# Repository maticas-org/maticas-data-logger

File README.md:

# Maticas datalogger 🚀⭐️

Want to send measurements back to a server through HTTP or MQTT? This is about it along with:

- The PCB design 🤖.
    - The schematic.
    - The PCB layout.
    - Source files for KiCad.
- 3D design 🗿:
    - The enclosure.
    - The sensor holder, stevenson screen.
- Code for the ESP32 💻.
    - Arduino code.

### ESP32 [Bee-Data-Logger](https://github.com/strid3r21/Bee-Data-Logger) Based 🐝

The ESP32 Bee-Data-Logger based solution is a data logger based on the development from [them](https://github.com/strid3r21/Bee-Data-Logger).

It is intended to be final product, we grabbed the schematic pdf they provided and made a PCB design for it, sharing the KiCad files and the Gerber files, so you can make your own PCB, or have an easier time modifying the design.

If you want to find out more about the ESP32 Bee-Data-Logger based solution, check out the [ESP32 Bee-Data-Logger based PCB design doc](/pcb/datalogger-bee-based/).

### ESP32 Dev Board 🔧

The ESP32 Dev Board is a development board with an ESP32 microcontroller. Intended for prototyping and development, but you could use it for a final product. 

If want to find out more about the ESP32 Dev Board, check out the [ESP32 Dev Board code](/src/arduino/datalogger-esp32-dev-board/) and the [ESP32 Dev Board PCB design doc](/pcb/datalogger-esp32-dev-board/).

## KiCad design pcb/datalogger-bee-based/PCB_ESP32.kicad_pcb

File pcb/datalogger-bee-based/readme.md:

# This file is inspired on the work of the [Bee-Data-Logger](https://github.com/strid3r21/Bee-Data-Logger) project

Basically we took the schematics they shared and a bit of the layout we get from their [youtube video](https://youtu.be/vbtSqaVAqRw?si=KjJlswMw_XBVi3_l) and we made our own version of the datalogger, sharing the source files from kiCad to make it easier for others to replicate the project.

This PCB replica is undergoing testing and will be updated as soon as we have more information.

Huge thanks to the [Bee-Data-Logger](https://github.com/strid3r21/Bee-Data-Logger) project for sharing their work, it was a great inspiration for us, and a huge help to get started with our own datalogger project. Go check their project out! Give them a star️ ⭐️⭐️⭐! 

Please consider that the latest finished PCB version is [PCB_ESP32.kicad_pro](PCB_ESP32.kicad_pro), this is built on top of Kicad 8.0. So far we don't have code along for this project, so if you are interested in replicating this project, you will need to adapt the code from the [Bee-Data-Logger](https://github.com/strid3r21/Bee-Data-Logger)

## Schematics

## PCB Overview

## PCB 3D View

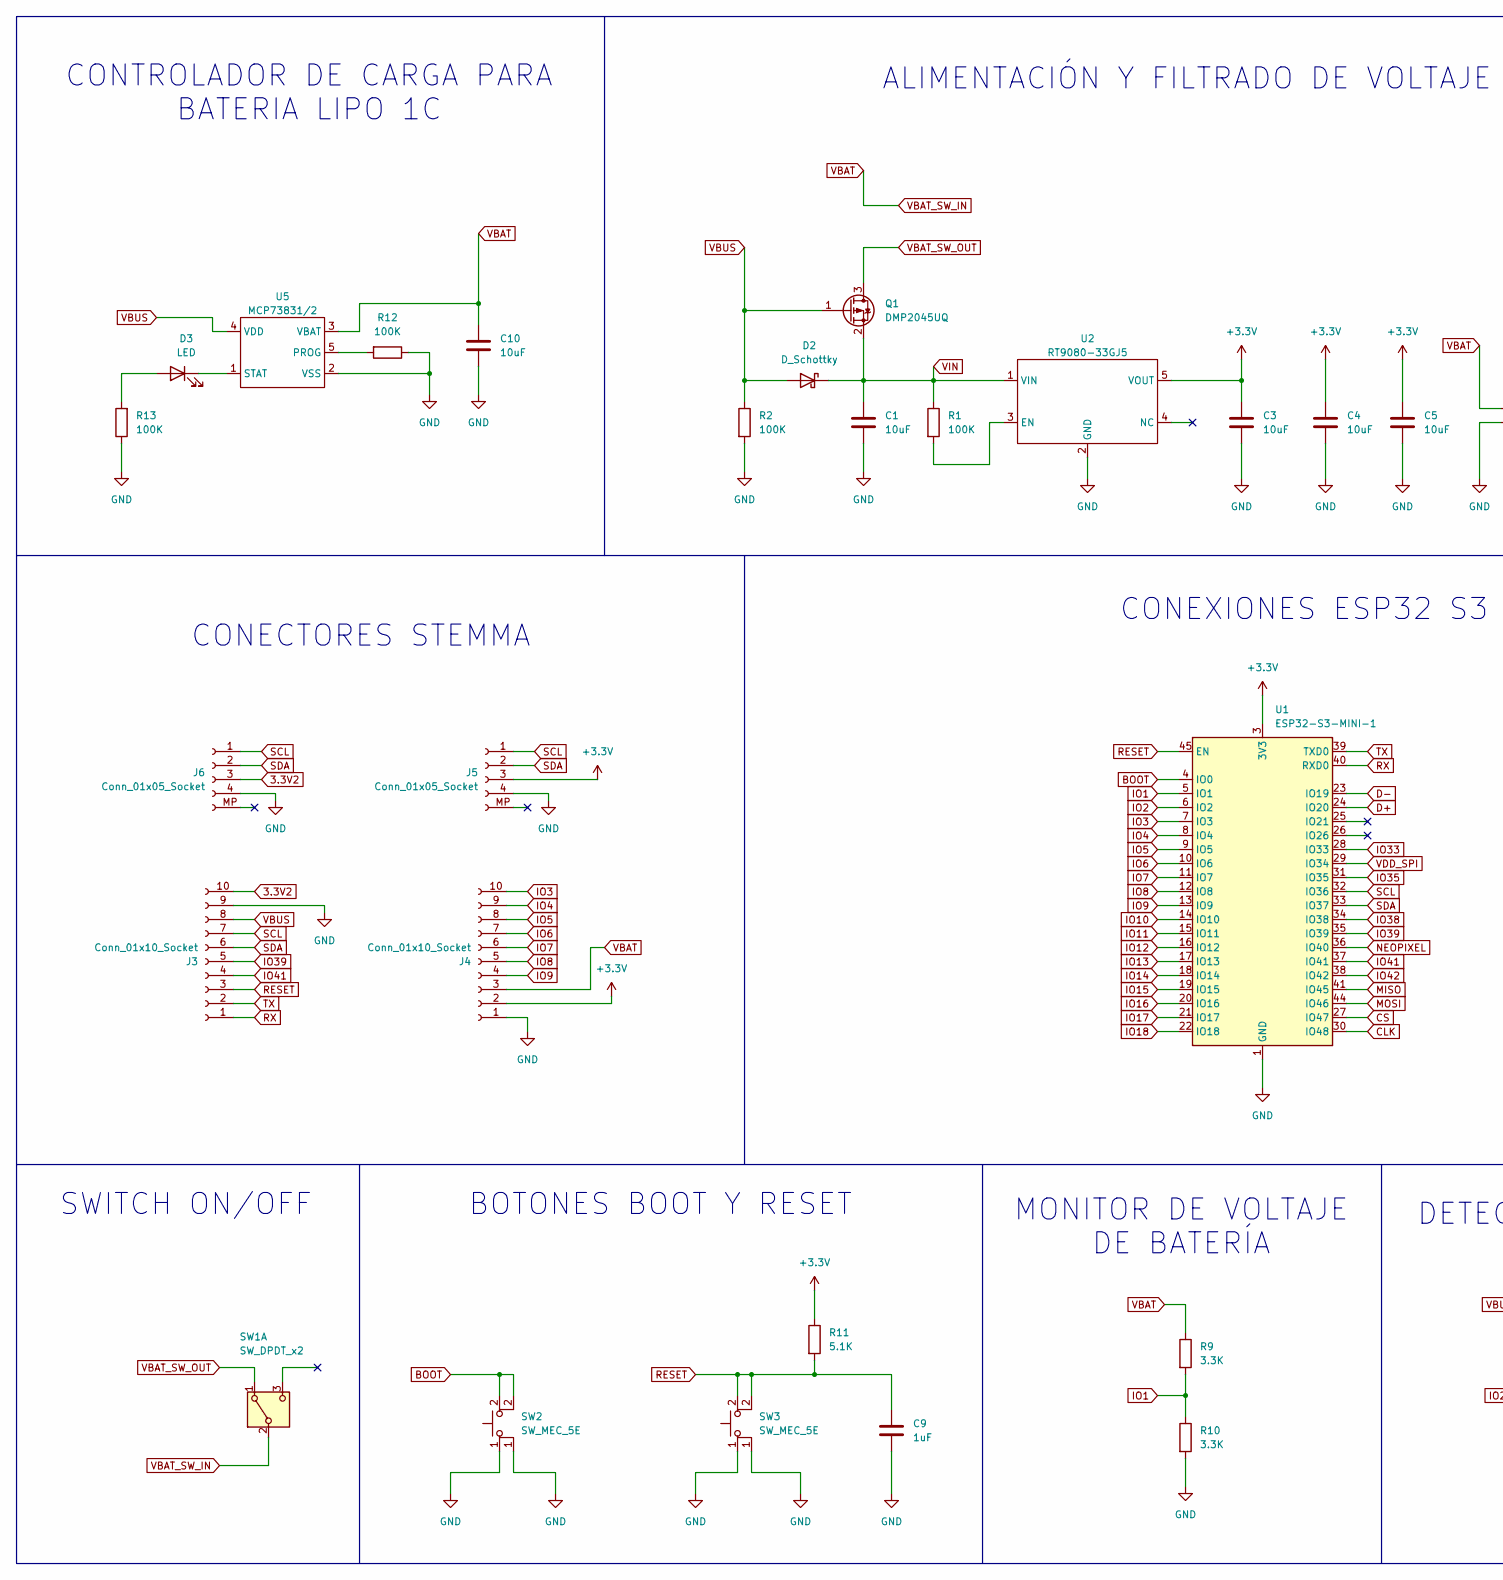
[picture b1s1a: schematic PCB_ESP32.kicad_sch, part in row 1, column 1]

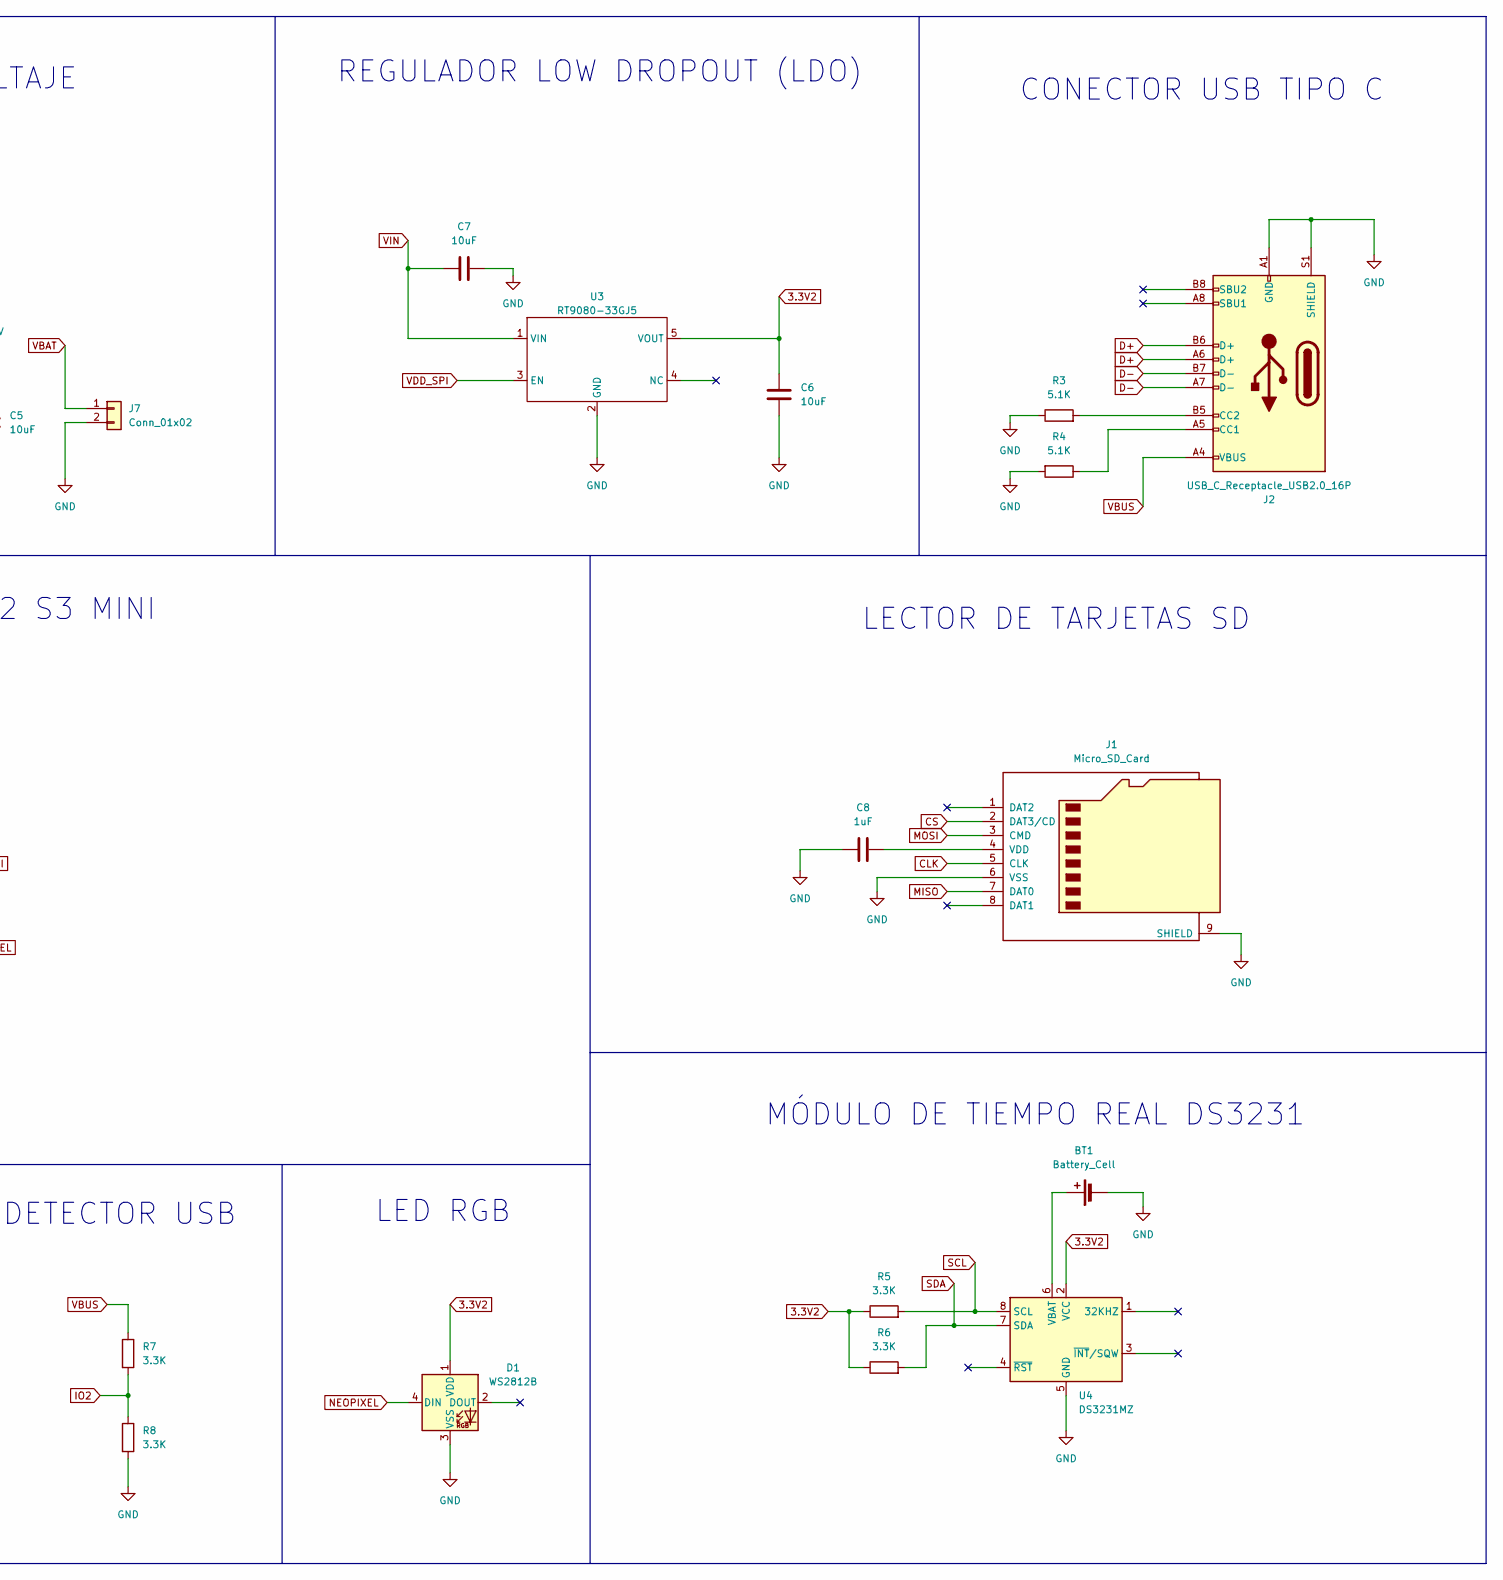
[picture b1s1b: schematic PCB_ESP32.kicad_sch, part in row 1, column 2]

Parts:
BT1: Battery_Cell; BatteryHolder_Keystone_1060_1x2032
C1, C3, C4, C5, C6, C7, C10: 10uF; C_0603_1608Metric
C8, C9: 1uF; C_0603_1608Metric
D1: WS2812B; LED_WS2812B-2020_PLCC4_2.0x2.0mm
D2: D_Schottky; DO-214AC
D3: LED; LED_0603_1608Metric
J1: Micro_SD_Card; microSD_HC_Hirose_DM3BT-DSF-PEJS
J2: USB_C_Receptacle_USB2.0_16P; USB_C_Receptacle_XKB_U262-16XN-4BVC11
J3, J4: Conn_01x10_Socket; PinHeader_1x10_P2.54mm_Vertical
J5, J6: Conn_01x05_Socket; JST_ACH_BM04B-ACHSS-A-GAN-ETF_1x04-1MP_P1.20mm_Vertical
J7: Conn_01x02; JST_ACH_BM02B-ACHSS-GAN-ETF_1x02-1MP_P1.20mm_Vertical
Q1: DMP2045UQ; SOT-23
R1, R2, R12, R13: 100K; R_0603_1608Metric
R3, R4, R11: 5.1K; R_0603_1608Metric
R5, R6, R7, R8, R9, R10: 3.3K; R_0603_1608Metric
SW1: SW_DPDT_x2; SW_SPDT_CK_JS102011SAQN
SW2, SW3: SW_MEC_5E; SW_SPST_PTS810
U1: ESP32-S3-MINI-1; ESP32-S2-MINI-1
U2, U3: RT9080-33GJ5; TSOT-23-5
U4: DS3231MZ; SOIC-8_3.9x4.9mm_P1.27mm
U5: MCP73831/2; SOT-23-5

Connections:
3.3V2: C6.1, D1.1 (VDD), J3.10, J6.3, R5.1, R6.1, U3.5 (VOUT), U4.2 (VCC)
+3.3V: C3.1, C4.1, C5.1, J4.2, J5.3, R11.1, U1.3 (3V3), U2.5 (VOUT)
BOOT: SW2.2, U1.4 (IO0)
CLK: J1.5 (CLK), U1.30 (IO48)
CS: J1.2 (DAT3/CD), U1.27 (IO47)
D+: J2.A6 (D+), J2.B6 (D+), U1.24 (IO20)
D-: J2.A7 (D-), J2.B7 (D-), U1.23 (IO19)
GND: BT1.2 (-), C1.2, C3.2, C4.2, C5.2, C6.2, C7.2, C8.1, C9.2, C10.2, D1.3 (VSS), J1.6 (VSS), J1.9 (SHIELD), J2.A1 (GND), J2.A12 (GND), J2.B1 (GND), J2.B12 (GND), J2.S1 (SHIELD), J3.9, J4.1, J5.4, J6.4, J7.2, R2.2, R3.1, R4.2, R8.2, R10.2, R12.1, R13.1, SW2.1, SW3.1, U1.1 (GND), U1.2 (GND), U1.42 (GND), U1.43 (GND), U1.46 (GND), U1.47 (GND), U1.48 (GND), U1.49 (GND), U1.50 (GND), U1.51 (GND), U1.52 (GND), U1.53 (GND), U1.54 (GND), U1.55 (GND), U1.56 (GND), U1.57 (GND), U1.58 (GND), U1.59 (GND), U1.60 (GND), U1.61 (GND), U1.62 (GND), U1.63 (GND), U1.64 (GND), U1.65 (GND), U2.2 (GND), U3.2 (GND), U4.5 (GND), U5.2 (VSS)
IO1: R9.2, R10.1, U1.5 (IO1)
IO2: R7.2, R8.1, U1.6 (IO2)
IO3: J4.10, U1.7 (IO3)
IO4: J4.9, U1.8 (IO4)
IO5: J4.8, U1.9 (IO5)
IO6: J4.7, U1.10 (IO6)
IO7: J4.6, U1.11 (IO7)
IO8: J4.5, U1.12 (IO8)
IO9: J4.4, U1.13 (IO9)
IO10: U1.14 (IO10)
IO11: U1.15 (IO11)
IO12: U1.16 (IO12)
IO13: U1.17 (IO13)
IO14: U1.18 (IO14)
IO15: U1.19 (IO15)
IO16: U1.20 (IO16)
IO17: U1.21 (IO17)
IO18: U1.22 (IO18)
IO33: U1.28 (IO33)
IO35: U1.31 (IO35)
IO38: U1.34 (IO38)
IO39: J3.5, U1.35 (IO39)
IO41: J3.4, U1.37 (IO41)
IO42: U1.38 (IO42)
MISO: J1.7 (DAT0), U1.41 (IO45)
MOSI: J1.3 (CMD), U1.44 (IO46)
NEOPIXEL: D1.4 (DIN), U1.36 (IO40)
unnamed: BT1.1 (+), U4.6 (VBAT)
unnamed: D3.2 (A), R13.2
unnamed: D3.1 (K), U5.1 (STAT)
unnamed: C8.2, J1.4 (VDD)
unnamed: J2.A5 (CC1), R4.1
unnamed: J2.B5 (CC2), R3.2
unnamed: R1.2, U2.3 (EN)
unnamed: R12.2, U5.5 (PROG)
RESET: C9.1, J3.3, R11.2, SW3.2, U1.45 (EN)
RX: J3.1, U1.40 (RXD0)
SCL: J3.7, J5.1, J6.1, R5.2, U1.32 (IO36), U4.8 (SCL)
SDA: J3.6, J5.2, J6.2, R6.2, U1.33 (IO37), U4.7 (SDA)
TX: J3.2, U1.39 (TXD0)
VBAT: C10.1, J4.3, J7.1, R9.1, SW1.2 (B), U5.3 (VBAT)
VBAT_SW_OUT: Q1.3 (D), SW1.1 (A)
VBUS: D2.2 (A), J2.A4 (VBUS), J2.A9 (VBUS), J2.B4 (VBUS), J2.B9 (VBUS), J3.8, Q1.1 (G), R2.1, R7.1, U5.4 (VDD)
VDD_SPI: U1.29 (IO34), U3.3 (EN)
VIN: C1.1, C7.1, D2.1 (K), Q1.2 (S), R1.1, U2.1 (VIN), U3.1 (VIN)

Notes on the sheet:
LED RGB
CONEXIONES ESP32 S3 MINI
CONECTORES STEMMA
MONITOR DE VOLTAJE DE BATERÍA
LECTOR DE TARJETAS SD
SWITCH ON/OFF
ALIMENTACIÓN Y FILTRADO DE VOLTAJE
BOTONES BOOT Y RESET
DETECTOR USB
MÓDULO DE TIEMPO REAL DS3231
CONECTOR USB TIPO C
CONTROLADOR DE CARGA PARA BATERIA LIPO 1C
REGULADOR LOW DROPOUT (LDO)

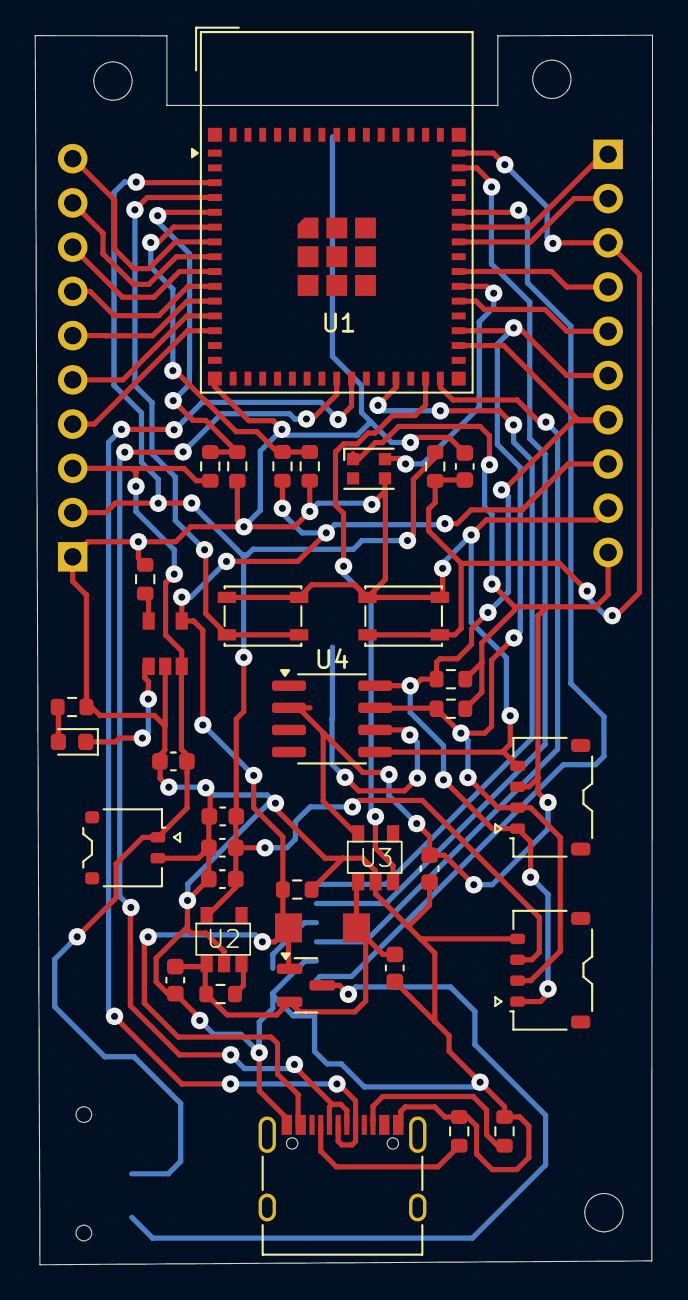
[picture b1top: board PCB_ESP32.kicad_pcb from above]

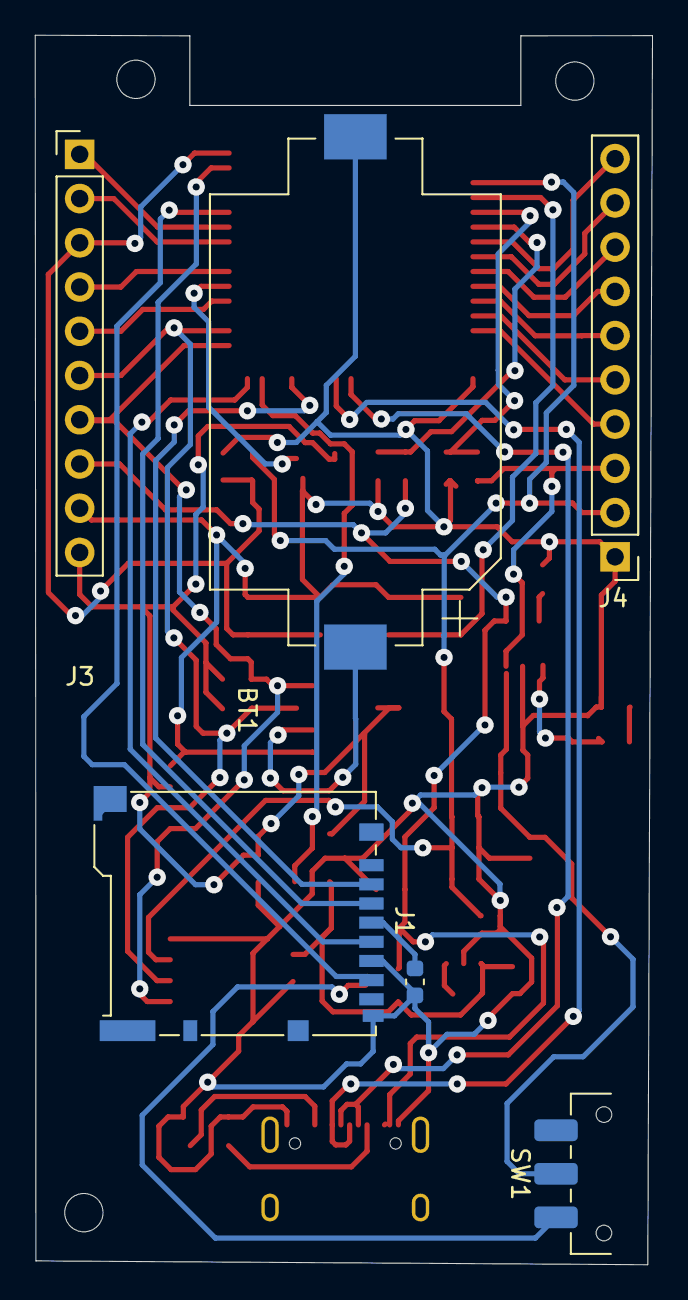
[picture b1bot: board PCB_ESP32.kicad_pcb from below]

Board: 2 copper layers, 35.4 x 70.6 mm, 42 parts (6 on the bottom side), 40 nets.

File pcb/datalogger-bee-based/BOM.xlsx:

No. | Quantity | Footprint | Designator |  | Comment | Manufacturer Part | Manufacturer | Supplier Part | Supplier | Primary Category | Secondary Category | Device | Name
1 | 1 | Device_Battery_Cell | BT1 |  | 1060TR |  |  | C238069 |  |  |  | Device_Battery_Cell | Device_Battery_Cell
2 | 7 | Device_C | C1,C3,C4,C5,C6,C7,C10 |  | 10uF |  |  | C96446 |  |  |  | Device_C | Device_C
3 | 2 | Device_C | C8,C9 |  | 1uF |  |  | C15849 |  |  |  | Device_C | Device_C
4 | 1 | LED_WS2812B | D1 |  | WS2812B |  |  | C965555 |  |  |  | LED_WS2812B | LED_WS2812B
5 | 1 | Device_D_Schottky | D2 |  | ss14 |  |  | C2480 |  |  |  | Device_D_Schottky | Device_D_Schottky
6 | 1 | Device_LED | D3 |  | XL-1608SURC-06 |  |  | C965799 |  |  |  | Device_LED | Device_LED
7 | 1 | Connector_Micro_SD_Card | J1 |  | DM3BT-DSF-PEJS |  |  | C597972 |  |  |  | Connector_Micro_SD_Card | Connector_Micro_SD_Card
8 | 1 | Connector_USB_C_Receptacle_USB2.0_16P | J2 |  | U262-161N-4BVC11 |  |  | C319148 |  |  |  | Connector_USB_C_Receptacle_USB2.0_16P | Connector_USB_C_Receptacle_USB2.0_16P
9 | 2 | Connector_Conn_01x10_Socket | J3,J4 |  | Conn_01x10_Socket |  |  | C2894933 |  |  |  | Connector_Conn_01x10_Socket | Connector_Conn_01x10_Socket
10 | 2 | Connector_Conn_01x05_Socket | J5,J6 |  | Conn_01x05_Socket |  |  | C528030 |  |  |  | Connector_Conn_01x05_Socket | Connector_Conn_01x05_Socket
11 | 1 | Connector_Generic_Conn_01x02 | J7 |  | Conn_01x02 |  |  | C202104 |  |  |  | Connector_Generic_Conn_01x02 | Connector_Generic_Conn_01x02
12 | 1 | Transistor_FET_AO3401A | Q1 |  | DMP2045UQ |  |  | C3290014 |  |  |  | Transistor_FET_AO3401A | Transistor_FET_AO3401A
13 | 4 | Device_R | R1,R2,R12,R13 |  | 100K |  |  | C25803 |  |  |  | Device_R | Device_R
14 | 3 | Device_R | R3,R4,R11 |  | 5.1K |  |  | C23186 |  |  |  | Device_R | Device_R
15 | 6 | Device_R | R5,R6,R7,R8,R9,R10 |  | 3.3K |  |  | C22978 |  |  |  | Device_R | Device_R
16 | 1 | Switch_SW_DPDT_x2 | SW1 |  | SW_DPDT_x2 |  |  | C221660 |  |  |  | Switch_SW_DPDT_x2 | Switch_SW_DPDT_x2
17 | 2 | Switch_SW_MEC_5E | SW2,SW3 |  | SW_MEC_5E |  |  | C221896 |  |  |  | Switch_SW_MEC_5E | Switch_SW_MEC_5E
18 | 1 | RF_Module_ESP32-S3-MINI-1 | U1 | BULETM-SMD_ESP32-S3-MINI-1-N8 | ESP32-S3-MINI-1-N8 |  |  | C2913206 |  |  |  | RF_Module_ESP32-S3-MINI-1 | RF_Module_ESP32-S3-MINI-1
19 | 1 | Bee-Data-Logger-library_rt9080-33GJ5 | U2 |  | RT9080-33GJ5 |  |  | C2959864 |  |  |  | Bee-Data-Logger-library_rt9080-33GJ5 | Bee-Data-Logger-library_rt9080-33GJ5
20 | 1 | Bee-Data-Logger-library_rt9080-33GJ5 | U3 |  | RT9080-33GJ5 |  |  | C841192 |  |  |  | Bee-Data-Logger-library_rt9080-33GJ5 | Bee-Data-Logger-library_rt9080-33GJ5
21 | 1 | Timer_RTC_DS3231MZ | U4 |  | DS3231MZ |  |  | C107410 |  |  |  | Timer_RTC_DS3231MZ | Timer_RTC_DS3231MZ
22 | 1 | Bee-Data-Logger-library_MCP73831/2 | U5 |  | MCP73831/2 |  |  | C625597 |  |  |  | Bee-Data-Logger-library_MCP73831/2 | Bee-Data-Logger-library_MCP73831/2

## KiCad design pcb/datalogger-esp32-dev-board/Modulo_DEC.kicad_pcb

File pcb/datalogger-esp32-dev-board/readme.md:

# ESP32 based datalogger development board

This board was designed to be a development board for the ESP32 based datalogger project. It is a simple board with capacity for few sensors and a microSD card slot, along with an RTC. This board is not meant to be a final product, but a development board to help with the development of the datalogger project, does not have a battery management system.

## Features

You can connect:

1. Multiple I2C sensors.
2. 1x Analog sensor.
3. 2x Digital sensor (with pull-up resistor).

And it has:
- MicroSD card slot.
- RTC.

## Product view 

## Schematics

## PCB Overview

## PCB 3D View

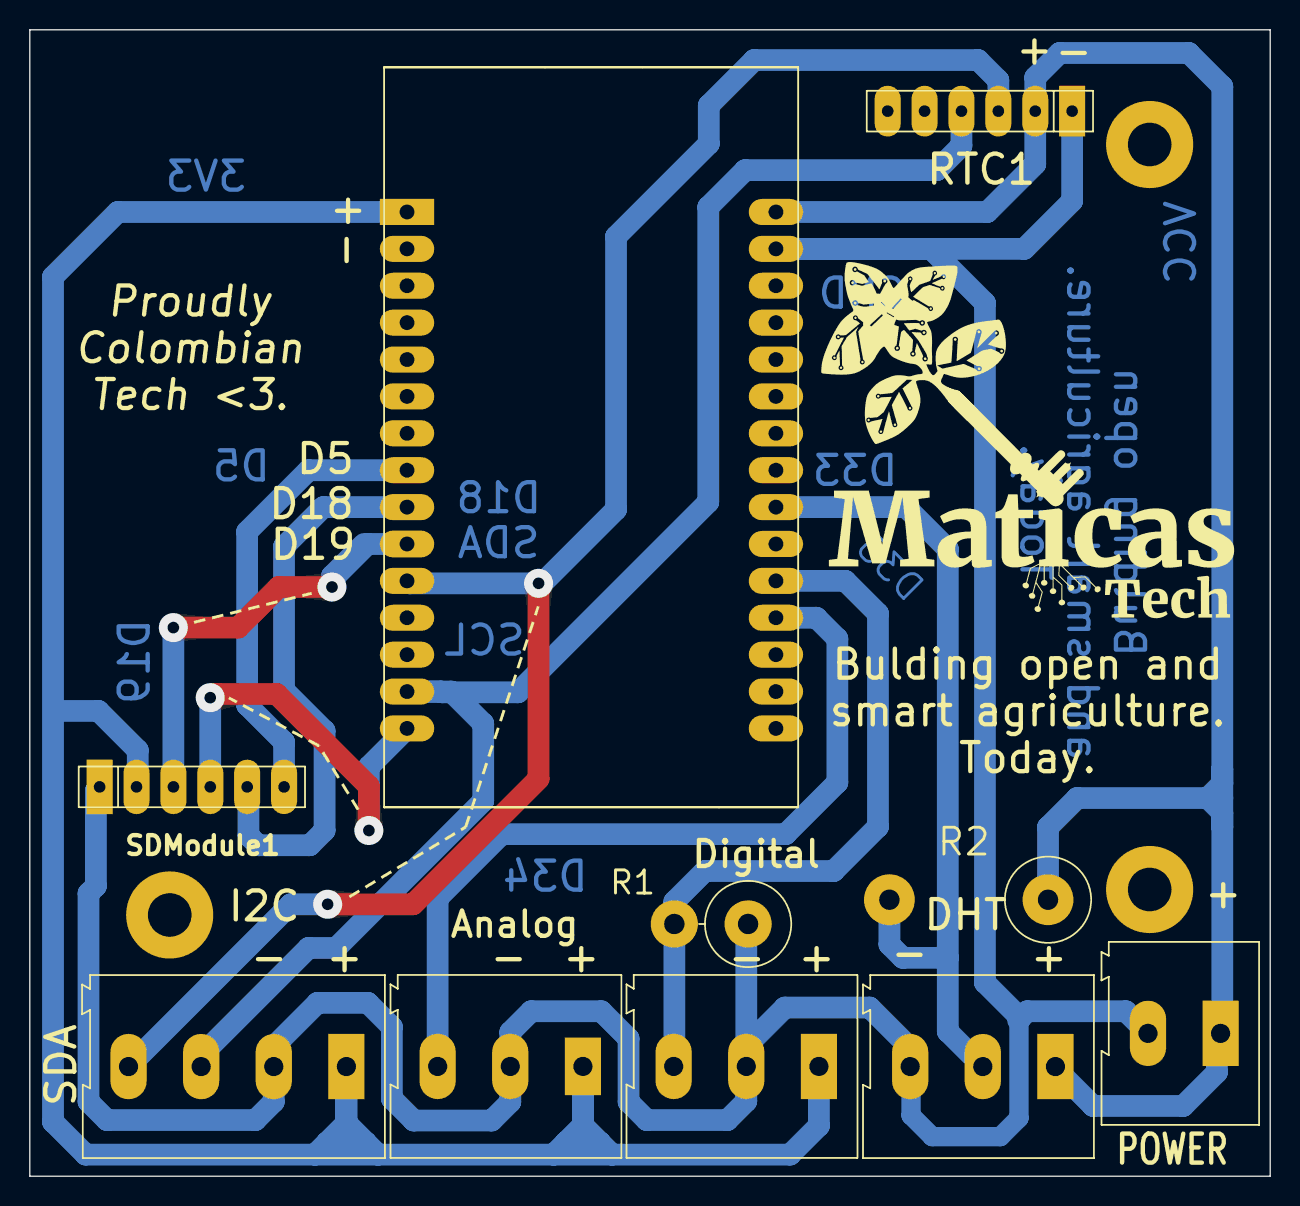
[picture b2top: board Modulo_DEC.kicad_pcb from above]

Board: 2 copper layers, 85.4 x 78.9 mm, 13 parts (0 on the bottom side), 12 nets.

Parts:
H1, H2, H3: MountingHole; MountingHole_3mm_Pad
J1: Screw_Terminal_01x04; TerminalBlock_Altech_AK300-4_P5.00mm
J2, J3, J4: Screw_Terminal_01x03; TerminalBlock_Altech_AK300-3_P5.00mm
J5: Screw_Terminal_01x02; TerminalBlock_Altech_AK300-2_P5.00mm
R1, R2: R; R_Axial_DIN0614_L14.3mm_D5.7mm_P5.08mm_Vertical
RTC1: R_Array_SIP6
SDModule1: R_Network_Dividers_x04_SIP; R_Array_SIP6
U1: ESP32-DEVKIT-V1; MODULE_ESP32_DEVKIT_V1

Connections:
3V3: J1.1, J2.1, J3.1, SDModule1.2 (R1), U1.1 (3V3)
D5: SDModule1.6 (COM2), U1.8 (D5)
D18: SDModule1.5 (R4), U1.9 (D18)
D19: SDModule1.3 (R2), U1.10 (D19)
D23: SDModule1.4 (R3), U1.15 (D23)
D33: J4.2, R2.2, U1.22 (D33)
D34: J2.3, U1.19 (D34)
D35: J3.3, R1.2, U1.20 (D35)
GND: J1.2, J2.2, J3.2, J4.3, J5.2, R1.1, RTC1.1 (COM1), SDModule1.1 (COM1), U1.2 (GND), U1.29 (GND)
SCL: J1.3, RTC1.4 (R3), U1.14 (D22)
SDA: J1.4, RTC1.3 (R2), U1.11 (D21)
VCC: J4.1, J5.1, R2.1, RTC1.2 (R1), U1.30 (VIN)

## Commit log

2024-05-09 first commit, added the PCB files, working source code and .stl files of the box
2024-10-05 add, added bee datalogger replication work
2024-10-05 update, added documentation for esp32 dev board, and renamed the src code folder for esp32 dev board to be more easy to understand code structure
2024-10-05 add, added documentation to main page
2024-11-06 update, PCB reviewed and sent to production, final testing remains to be done, added BOM and pos file, along with the outputs.zip used for fabrication
